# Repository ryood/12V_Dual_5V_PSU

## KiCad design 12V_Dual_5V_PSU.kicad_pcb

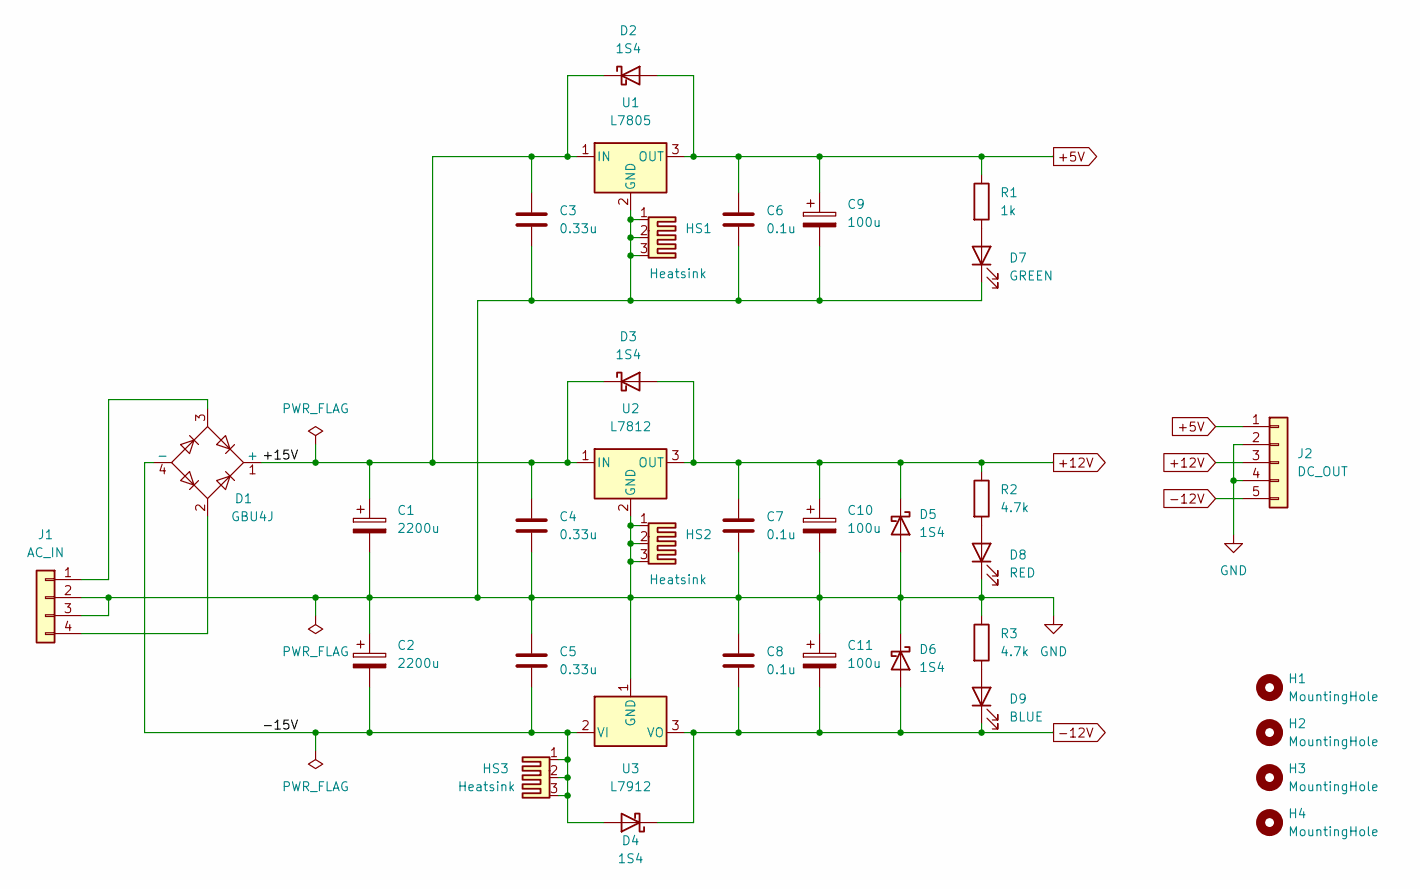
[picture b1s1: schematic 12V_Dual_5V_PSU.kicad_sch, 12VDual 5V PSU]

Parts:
C1, C2: 2200u; CP_Radial_D16.0mm_P7.50mm
C3, C4, C5: 0.33u; C_Disc_D3.0mm_W1.6mm_P2.50mm
C6, C7, C8: 0.1u; C_Disc_D3.0mm_W1.6mm_P2.50mm
C9, C10, C11: 100u; CP_Radial_D6.3mm_P2.50mm
D1: GBU4J; Diode_Bridge_Vishay_GBU
D2, D3, D4, D5, D6: 1S4; D_DO-35_SOD27_P7.62mm_Horizontal
D7: GREEN; LED_D3.0mm
D8: RED; LED_D3.0mm
D9: BLUE; LED_D3.0mm
H1, H2, H3, H4: MountingHole; MountingHole_3.2mm_M3
HS1, HS2, HS3: Heatsink; Heatsink_30PC030
J1: AC_IN; JST_XH_B4B-XH-A_1x04_P2.50mm_Vertical
J2: DC_OUT; JST_XH_B5B-XH-A_1x05_P2.50mm_Vertical
R1: 1k; R_Axial_DIN0207_L6.3mm_D2.5mm_P10.16mm_Horizontal
R2, R3: 4.7k; R_Axial_DIN0207_L6.3mm_D2.5mm_P10.16mm_Horizontal
U1: L7805; TO-220F-3_Vertical
U2: L7812; TO-220F-3_Vertical
U3: L7912; TO-220F-3_Vertical

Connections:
+5V: C6.1, C9.1, D2.2 (A), J2.1, R1.1, U1.3 (OUT)
+12V: C7.1, C10.1, D3.2 (A), D5.1 (K), J2.3, R2.1, U2.3 (OUT)
-12V: C8.2, C11.2, D4.1 (K), D6.2 (A), D9.1 (K), J2.5, U3.3 (VO)
/+15V: C1.1, C3.1, C4.1, D1.1 (+), D2.1 (K), D3.1 (K), U1.1 (IN), U2.1 (IN)
/-15V: C2.2, C5.2, D1.4 (-), D4.2 (A), HS3.1, HS3.2, HS3.3, U3.2 (VI)
GND: C1.2, C2.1, C3.2, C4.2, C5.1, C6.2, C7.2, C8.1, C9.2, C10.2, C11.1, D5.2 (A), D6.1 (K), D7.1 (K), D8.1 (K), HS1.1, HS1.2, HS1.3, HS2.1, HS2.2, HS2.3, J1.2, J1.3, J2.2, J2.4, R3.1, U1.2 (GND), U2.2 (GND), U3.1 (GND)
unnamed: D1.2, J1.4
unnamed: D1.3, J1.1
unnamed: D7.2 (A), R1.2
unnamed: D8.2 (A), R2.2
unnamed: D9.2 (A), R3.2

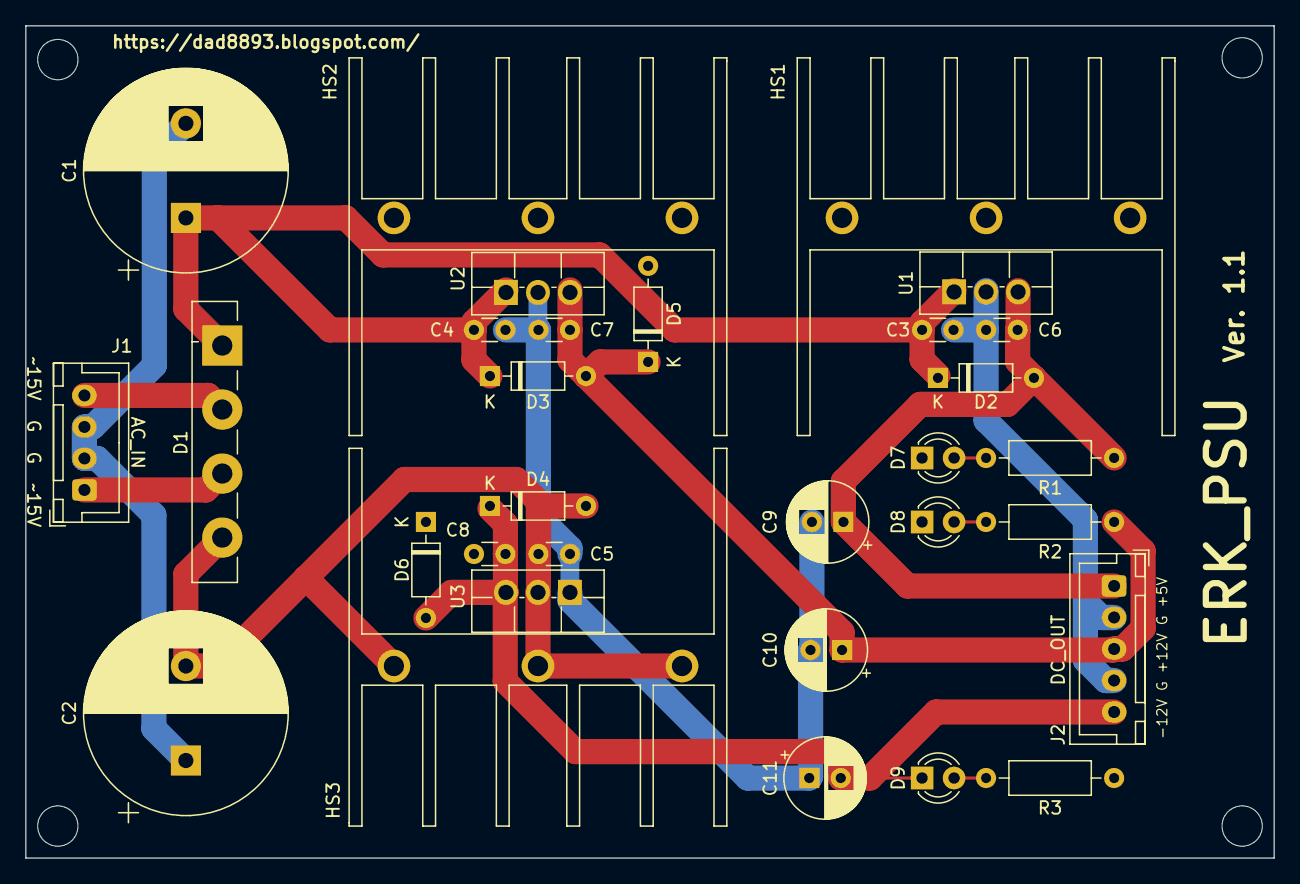
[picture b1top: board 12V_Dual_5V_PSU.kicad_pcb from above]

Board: 2 copper layers, 99.1 x 66.0 mm, 35 parts (0 on the bottom side), 11 nets.
